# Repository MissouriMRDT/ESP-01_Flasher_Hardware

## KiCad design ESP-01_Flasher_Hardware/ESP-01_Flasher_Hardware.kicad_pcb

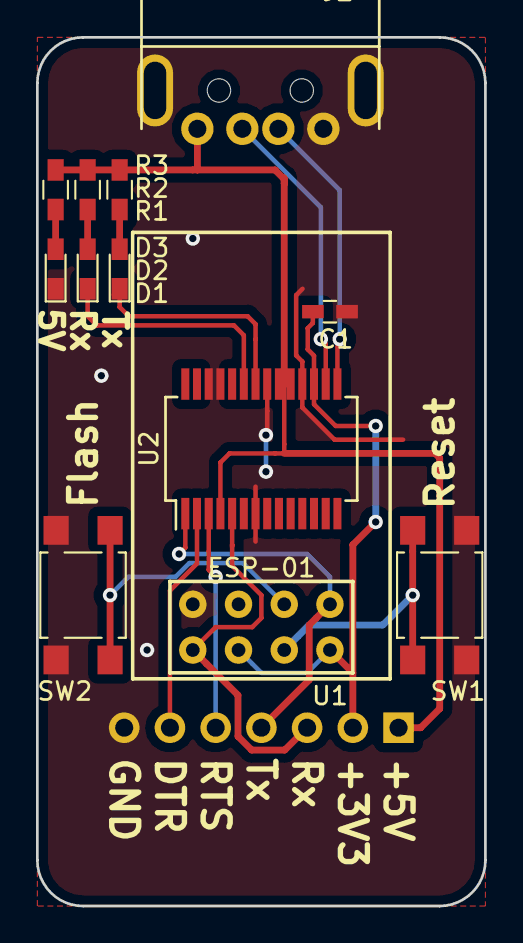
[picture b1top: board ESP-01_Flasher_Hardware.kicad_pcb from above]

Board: 2 copper layers, 24.9 x 48.3 mm, 13 parts (1 on the bottom side), 16 nets.

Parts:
C1: .1uF; C_0603_HandSoldering
D1: Tx; LED_0603_HandSoldering
D2: Rx; LED_0603_HandSoldering
D3: PWR; LED_0603_HandSoldering
J1: Conn_01x07_Female; Socket_Strip_Angled_1x07_Pitch2.54mm
J2: USB_A; USBA
R1, R2, R3: 330; R_0603_HandSoldering
SW1, SW2: SW_Push; SW_SPST_TL3305A
U1: ESP-01; ESP8266-01
U2: FT232RL; SSOP-28_5.3x10.2mm_Pitch0.65mm

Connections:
+3V3: C1.1, J1.2, U1.4, U1.8, U2.17
+5V: J1.1, J2.1, R1.1, R2.1, R3.1, U2.4, U2.19, U2.20
D+: J2.3, U2.15
D-: J2.2, U2.16
DTR: J1.6, U2.2
FT_Rx: J1.3, U1.2, U2.5
FT_Tx: J1.4, U1.7, U2.1
Flash: SW2.1, U1.5
GND: C1.2, D3.1, J1.7, J2.4, J2.5, SW1.2, SW2.2, U1.1, U2.7, U2.18, U2.21, U2.25, U2.26
unnamed: D1.1, U2.22
unnamed: D1.2, R1.2
unnamed: D2.1, U2.23
unnamed: D2.2, R2.2
unnamed: D3.2, R3.2
RTS: J1.5, U2.3
Rst: SW1.1, U1.6

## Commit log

2018-12-19 Created Schematic
2018-12-19 layout
